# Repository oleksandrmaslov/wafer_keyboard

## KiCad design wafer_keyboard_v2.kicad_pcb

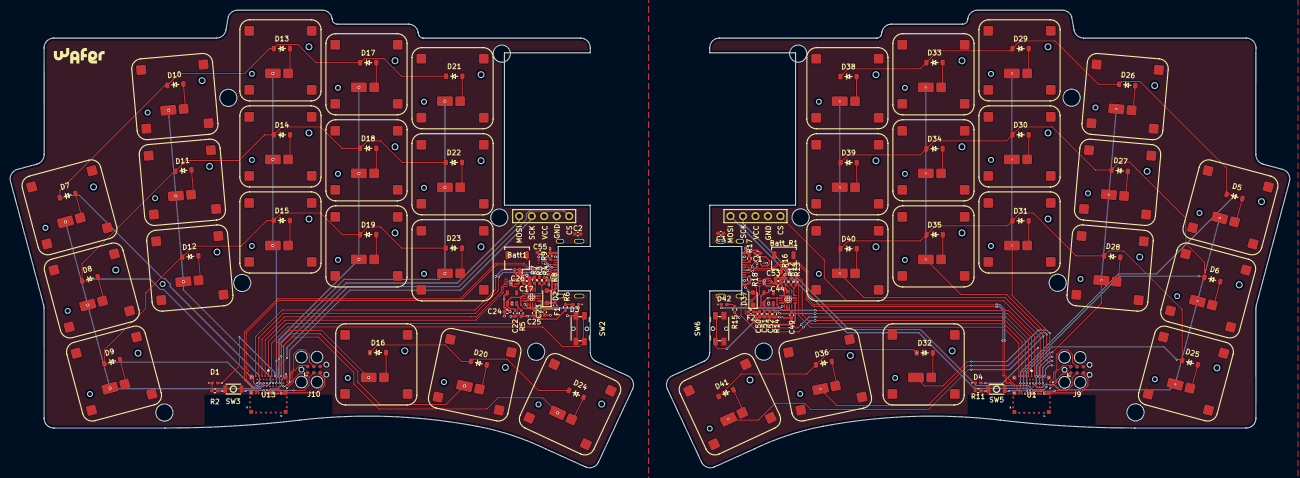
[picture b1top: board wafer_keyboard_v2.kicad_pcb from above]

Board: 4 copper layers, 260.2 x 93.0 mm, 134 parts (0 on the bottom side), 116 nets.

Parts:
Batt1: Conn_01x02; JST_SHL_SM02B-SHLS-TF_1x02-1MP_P1.00mm_Horizontal
Batt_R1: Conn_01x02; JST_SHL_SM02B-SHLS-TF_1x02-1MP_P1.00mm_Horizontal
C1, C24, C25, C26, C51, C52, C53, C55: 4.7uF; C_0402_1005Metric_Pad0.74x0.62mm_HandSolder
C2, C3: 10nF; C_0402_1005Metric_Pad0.74x0.62mm_HandSolder
C17, C44: 100nF; C_0402_1005Metric_Pad0.74x0.62mm_HandSolder
C22, C49: 10uF; C_0402_1005Metric_Pad0.74x0.62mm_HandSolder
C23, C50: 1uF; C_0402_1005Metric_Pad0.74x0.62mm_HandSolder
D1, D4: BLUE; LED_0402_1005Metric_Pad0.77x0.64mm_HandSolder
D2, D37: PMEG4010CEJ; D_SOD-323_HandSoldering
D3, D42: ORANGE; LED_0402_1005Metric_Pad0.77x0.64mm_HandSolder
D5, D6, D7, D8, D9, D10, D11, D12, D13, D14, D15, D16, D17, D18, D19, D20, D21, D22, D23, D24, D25, D26, D27, D28, D29, D30, D31, D32, D33, D34, D35, D36, D38, D39, D40, D41: Diode; Diode_SOD-123
F1, F2: 500mA hold; Fuse_0402_1005Metric_Pad0.77x0.64mm_HandSolder
J1, J5: USB_C_Receptacle_USB2.0; USB-C_C168688
J4, J6: nice!view; display_nice_view
J9, J10: Conn_ARM_SWD_TagConnect_TC2030; Tag-Connect_TC2030-IDC-FP_2x03_P1.27mm_Vertical
R2, R11: 1.5k; R_0402_1005Metric_Pad0.72x0.64mm_HandSolder
R3, R6, R7, R12, R15, R16: 10k; R_0402_1005Metric_Pad0.72x0.64mm_HandSolder
R4, R13: 3.9k; R_0402_1005Metric_Pad0.72x0.64mm_HandSolder
R5, R14: 2M; R_0402_1005Metric_Pad0.72x0.64mm_HandSolder
R8, R9, R17, R18: 5.1k; R_0402_1005Metric_Pad0.72x0.64mm_HandSolder
S1, S2, S3, S4, S5, S6, S7, S8, S9, S10, S11, S12, S13, S14, S15, S16, S17, S18, S19, S20, S21, S22, S23, S24, S25, S26, S27, S28, S29, S30, S31, S32, S33, S34, S35, S36: Keyswitch; CPG1316S01D02_front_mikefives
SW2, SW6: Soft-off switch; Panasonic_EVQPUL_EVQPUC
SW3, SW5: Reset; SW-SMD_L3.0-W2.0-LS3.5
U1, U13: ISP1807-LR-RS
U2, U8: MAX17048; TDFN-8-1EP_2x2mm_P0.5mm_EP0.8x1.2mm
U3, U9: BQ24075RGT; VQFN-16-1EP_3x3mm_P0.5mm_EP1.6x1.6mm
U4, U10: XC6220B331MR; SOT-23-5
U6, U12: ESDR0502NMUTAG; UDFN-6_1.2x1.0mm_P0.4mm

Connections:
/CC1: J1.A5 (CC1), R8.1
/CC2: J1.B5 (CC2), R9.1
/Right side pcb/CC1: J5.A5 (CC1), R17.1
/Right side pcb/CC2: J5.B5 (CC2), R18.1
BAT_I2C_SCL: U2.7 (SCL), U13.44 (P0_30_AIN6)
BAT_I2C_SCL R: U1.44 (P0_30_AIN6), U8.7 (SCL)
BAT_I2C_SDA: U2.8 (SDA), U13.42 (P0_31_AIN7)
BAT_I2C_SDA R: U1.42 (P0_31_AIN7), U8.8 (SDA)
BLUE_LED: D1.2 (A), U13.36 (P0_05_AIN3)
BLUE_LED R: D4.2 (A), U1.36 (P0_05_AIN3)
CHARGE_CTRL_1: R3.1, U13.46 (P0_29_AIN5)
CHARGE_CTRL_1 R: R12.1, U1.46 (P0_29_AIN5)
CHARGE_CTRL_2: R4.2, U13.48 (P0_28_AIN4)
CHARGE_CTRL_2 R: R13.2, U1.48 (P0_28_AIN4)
Col 0: S4.1, S5.1, S6.1, U13.52 (P1_14)
Col 0 R: S1.1, S2.1, S3.1, U1.52 (P1_14)
Col 1: S7.1, S8.1, S9.1, U13.51 (P1_15)
Col 1 R: S22.1, S23.1, S24.1, U1.51 (P1_15)
Col 2: S10.1, S11.1, S12.1, S13.1, U13.50 (P1_06)
Col 2 R: S25.1, S26.1, S27.1, S28.1, U1.50 (P1_06)
Col 3: S14.1, S15.1, S16.1, S17.1, U13.49 (P1_02)
Col 3 R: S29.1, S30.1, S31.1, S32.1, U1.49 (P1_02)
Col 4: S18.1, S19.1, S20.1, S21.1, U13.32 (P0_08)
Col 4 R: S33.1, S34.1, S35.1, S36.1, U1.32 (P0_08)
GND: Batt1.1, C2.1, C17.1, C22.1, C23.2, C24.1, C25.1, C26.1, C55.1, J1.A1 (GND), J4.4, J10.5 (GND), R2.1, R5.2, R7.2, R8.2, R9.2, SW2.2, SW3.2, U2.1 (CTG), U2.4 (GND), U2.6 (QSTRT), U2.9 (EP), U3.4 (~CE), U3.5 (EN2), U3.8 (VSS), U3.15 (SYSOFF), U3.17 (VSS), U4.2 (GND), U6.1 (GND), U13.1 (VSS), U13.7 (VSS), U13.14 (VSS), U13.16 (VSS), U13.18 (VSS), U13.21 (VSS), U13.23 (VSS), U13.24 (VSS), U13.25 (VSS), U13.31 (VSS)
GND 1: Batt_R1.1, C1.1, C3.1, C44.1, C49.1, C50.2, C51.1, C52.1, C53.1, J5.A1 (GND), J6.4, J9.5 (GND), R11.1, R14.2, R16.2, R17.2, R18.2, SW5.2, SW6.2, U1.1 (VSS), U1.7 (VSS), U1.14 (VSS), U1.16 (VSS), U1.18 (VSS), U1.21 (VSS), U1.23 (VSS), U1.24 (VSS), U1.25 (VSS), U1.31 (VSS), U8.1 (CTG), U8.4 (GND), U8.6 (QSTRT), U8.9 (EP), U9.4 (~CE), U9.5 (EN2), U9.8 (VSS), U9.15 (SYSOFF), U9.17 (VSS), U10.2 (GND), U12.1 (GND)
unnamed: C2.2, J1.S1 (SHIELD)
unnamed: C3.2, J5.S2 (SHIELD)
unnamed: D1.1 (K), R2.2
unnamed: D2.1 (K), F1.2
unnamed: D3.2 (A), R6.2
unnamed: D3.1 (K), U3.9 (~CHG)
unnamed: D4.1 (K), R11.2
unnamed: D5.2 (A), S1.2
unnamed: D6.2 (A), S2.2
unnamed: D7.2 (A), S4.2
unnamed: D8.2 (A), S5.2
unnamed: D9.2 (A), S6.2
unnamed: D10.2 (A), S7.2
unnamed: D11.2 (A), S8.2
unnamed: D12.2 (A), S9.2
unnamed: D13.2 (A), S10.2
unnamed: D14.2 (A), S11.2
unnamed: D15.2 (A), S12.2
unnamed: D16.2 (A), S13.2
unnamed: D17.2 (A), S14.2
unnamed: D18.2 (A), S15.2
unnamed: D19.2 (A), S16.2
unnamed: D20.2 (A), S17.2
unnamed: D21.2 (A), S18.2
unnamed: D22.2 (A), S19.2
unnamed: D23.2 (A), S20.2
unnamed: D24.2 (A), S21.2
unnamed: D25.2 (A), S3.2
unnamed: D26.2 (A), S22.2
unnamed: D27.2 (A), S23.2
unnamed: D28.2 (A), S24.2
unnamed: D29.2 (A), S25.2
unnamed: D30.2 (A), S26.2
unnamed: D31.2 (A), S27.2
unnamed: D32.2 (A), S28.2
unnamed: D33.2 (A), S29.2
unnamed: D34.2 (A), S30.2
unnamed: D35.2 (A), S31.2
unnamed: D36.2 (A), S32.2
unnamed: D37.1 (K), F2.2
unnamed: D38.2 (A), S33.2
unnamed: D39.2 (A), S34.2
unnamed: D40.2 (A), S35.2
unnamed: D41.2 (A), S36.2
unnamed: D42.2 (A), R15.2
unnamed: D42.1 (K), U9.9 (~CHG)
unnamed: U1.20 (OUT_ANT), U1.22 (OUT_MOD)
unnamed: C23.1, F1.1, U3.13 (IN)
unnamed: R3.2, R4.1, U3.16 (ISET)
unnamed: R7.1, U3.1 (TS)
unnamed: C50.1, F2.1, U9.13 (IN)
unnamed: R12.2, R13.1, U9.16 (ISET)
unnamed: R16.1, U9.1 (TS)
unnamed: U13.20 (OUT_ANT), U13.22 (OUT_MOD)
P0.06: J4.5, U13.34 (P0_06)
P0.06 R: J6.5, U1.34 (P0_06)
P0.17: J4.2, U13.27 (P0_17)
P0.17 R: J6.2, U1.27 (P0_17)
P0.20: J4.1, U13.15 (P0_20)
P0.20 R: J6.1, U1.15 (P0_20)
PPH_VCC: C24.2, J4.3, J10.1 (VCC), U4.5 (VOUT), U13.26 (VCC_NRF)
PPH_VCC R: C51.2, J6.3, J9.1 (VCC), U1.26 (VCC_NRF), U10.5 (VOUT)
PPH_VCC_CTRL: R5.1, U4.3 (CE), U13.40 (P0_02_AIN0)
PPH_VCC_CTRL R: R14.1, U1.40 (P0_02_AIN0), U10.3 (CE)
RESET: J10.3 (~RESET), SW3.1, U13.13 (P0_18_RESET)
RESET R: J9.3 (~RESET), SW5.1, U1.13 (P0_18_RESET)
R_USB_D+: J5.A6 (D+), J5.B6 (D+), U1.8 (D+), U12.5 (D+)
R_USB_D-: J5.A7 (D-), J5.B7 (D-), U1.10 (D-), U12.4 (D-)
Row 0: D7.1 (K), D10.1 (K), D13.1 (K), D17.1 (K), D21.1 (K), U13.56 (P1_09_TRACEDATA3)
Row 0 R: D5.1 (K), D26.1 (K), D29.1 (K), D33.1 (K), D38.1 (K), U1.56 (P1_09_TRACEDATA3)
Row 1: D8.1 (K), D11.1 (K), D14.1 (K), D18.1 (K), D22.1 (K), U13.55 (P1_08)
Row 1 R: D6.1 (K), D27.1 (K), D30.1 (K), D34.1 (K), D39.1 (K), U1.55 (P1_08)
Row 2: D9.1 (K), D12.1 (K), D15.1 (K), D19.1 (K), D23.1 (K), U13.54 (P1_05)
Row 2 R: D25.1 (K), D28.1 (K), D31.1 (K), D35.1 (K), D40.1 (K), U1.54 (P1_05)
Row 3: D16.1 (K), D20.1 (K), D24.1 (K), U13.53 (P1_13)
Row 3 R: D32.1 (K), D36.1 (K), D41.1 (K), U1.53 (P1_13)
SWC: J10.4 (SWCLK), U13.30 (SWDCLK)
SWC R: J9.4 (SWCLK), U1.30 (SWDCLK)
SWD: J10.2 (SWDIO), U13.28 (SWDIO)
SWD R: J9.2 (SWDIO), U1.28 (SWDIO)
Soft-off: SW2.1, U13.38 (P0_03_AIN1)
Soft-off R: SW6.1, U1.38 (P0_03_AIN1)
USB_D+: J1.A6 (D+), J1.B6 (D+), U6.5 (D+), U13.8 (D+)
USB_D-: J1.A7 (D-), J1.B7 (D-), U6.4 (D-), U13.10 (D-)
VBAT: Batt1.2, C17.2, C26.2, U2.2 (CELL), U2.3 (VDD), U3.2 (BAT), U3.3 (BAT)
VBAT R: Batt_R1.2, C44.2, C53.2, U8.2 (CELL), U8.3 (VDD), U9.2 (BAT), U9.3 (BAT)
VBUS: C55.2, D2.2 (A), J1.A4 (VBUS), U6.6 (VBUS), U13.12 (VBUS)
VBUS R: C1.2, D37.2 (A), J5.A4 (VBUS), U1.12 (VBUS), U12.6 (VBUS)
VDDH: C22.2, C25.2, R6.1, U3.6 (EN1), U3.10 (OUT), U3.11 (OUT), U4.1 (VIN)
VDDH R: C49.2, C52.2, R15.1, U9.6 (EN1), U9.10 (OUT), U9.11 (OUT), U10.1 (VIN)
